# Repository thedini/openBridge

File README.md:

# openBridge

<<<<<<< HEAD
## Abstract

# The set-up

## Initial steps

The Adruino code for this project is based around the NMEA2000 and NMEA2000_Teensyx libraries created by Tino Lappalainen. These are utilized to send the NMEA2000 packets on to the wire.

=======
A project with the purpose of making, exploring and hacking NMEA2000 and marine electronics and making learning achievable without expensive hardware. The ultimate goal is to enable creation of bridge simulations that can be output onto an actual NMEA 2000 bus to enable exploration of the protocol and real world systems at scale. OpenBridge leverages the hard work of the community around these endeavors and hopes to standardize software and hardware as well as adding detailed documentation to low cost exposure to this technology to the wider maritime, engineering and maker/hacker community.

## The Mission

OpenBridge will attempt to leverage exiting work from [CanBoat](https://github.com/canboat/canboat) and [ttlappalaine NMEA 2000](https://github.com/ttlappalainen/NMEA2000) libraries to create a suite of micro-services (containers) that can serve as maritime electronic devices for learning, testing and simulation. By standardizing the hardware and software and having a focus on documentation OpenBridge hopes to make exploration open to groups that would normally not have access or ability to dive into the world of maritime electronics.

Ideally, each micro-service can act as if it is the authentic electronic device using the Teensy as a gateway to an actual ship or test NMEA 2000 bus. OpenBridge will grow to become a curriculum on NMEA 2000 analysis and shipboard security curriculum to provide the basis for self study or teaching! The hope is to give everyone the ability to explore this interesting niche of technology!

## Quick Start

1. Read up on the [CAN Protocol](docs/can_protocol.md)
2. Setup Arduino and Teensy on your system (external links)
3. Load up simple [example code](scr/ARDUINO/working_wind.ino) in Ardino
4. Check out [python documentation](docs/python.md) to extend your capability
5. Fork the repo and build your own!

## The Hardware

The hardware is based on the latest Teensy (4.0 and 4.1). The Teensy provides a huge capability for the price which will lend itself to expansion at a later time. The Teensy also has **three** CAN interfaces to enable further expansion. The Teensy will be mounted on breadboard, perf-board or custom PCB that will enable it to easily connect to an NEMA 2000 bus in a standard fashion. The idea of standardizing on hardware is born from the desire to have a standard platform to develop on and support. As can be expected, most of the associated code and procedures can be adapted for various other platform which are outside the scope of this project. (ESP32, Arduino Mega, Raspberry Pi)

The CAN interfaces will require CAN transceivers (VD230) to accommodate conversion from Can High and Can Low to Can TX and Can RX. These device have been chosen based on their general availability and price.

The system can be built on a Breadboard, or utilize custom PCB to accommodate NMEA 2000 plug. In its simplest implementation it requires little more than a Teensy, the VD230 and some hookup wires.

Specific hardware can be found in the [BoM](docs/bom.md) with board designs in [schmatics](schmatics/)

## Software

The software side of the OpenBridge is going to leverage [ttlappalaine NMEA 2000](https://github.com/ttlappalainen/NMEA2000) and [ttlappalaine's Teeensy Library](https://github.com/ttlappalainen/NMEA2000_Teensyx) as a base. Code is stored in the `src` directory and organized by function. Follow the `docs` to utilize open source code and open hardware to study NMEA2000.

In its most simple implementation you can use OpenBridge to start looking at data with one of many Logic Analyzers and learning how to decipher different parts of the NMEA2000 CAN Frame with the basic **wind sensor**

Extend the capability of the **wind sensor** by feeding your own wind parameters via a csv file.

## UPDATES

19OCT21: Huge push of updated code base. Completely refactored. Plan to add more documentation soon!
>>>>>>> f373c3691c084f3768c9d36196ce28ea740e8996

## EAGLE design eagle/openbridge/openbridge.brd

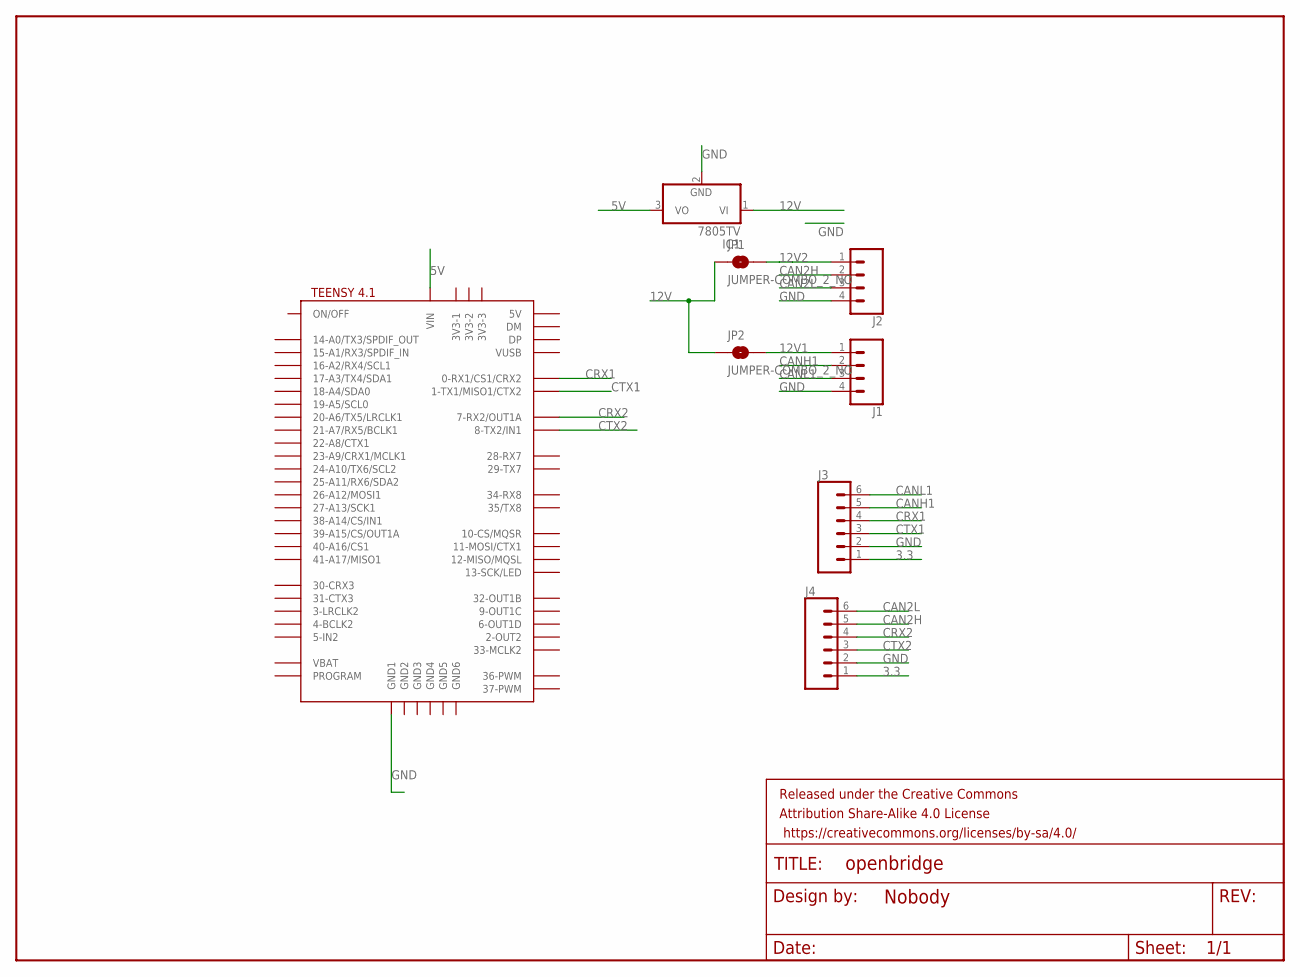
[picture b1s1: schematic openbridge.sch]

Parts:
FRAME1: FRAME-LETTERNO_PACKAGE; DUMMY
IC1: 7805TV; TO220V
J1, J2: CONN_04SCREW; SCREWTERMINAL-3.5MM-4
J3, J4: CONN_06LONGPADS; 1X06_LONGPADS
JP1, JP2: JUMPER-COMBO_2_NO; COMBO-JUMPER_2_NO
U$1: TEENSY41-E; TENNSY41-E

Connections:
3.3: J3.1, J4.1
5V: IC1.3 (VO), U$1.VIN
12V: IC1.1 (VI), JP1.1, JP1.3 (1), JP2.1, JP2.3 (1)
12V1: J1.1, JP2.2, JP2.4 (2)
12V2: J2.1, JP1.2, JP1.4 (2)
CAN2H: J2.2, J4.5
CAN2L: J2.3, J4.6
CANH1: J1.2, J3.5
CANL1: J1.3, J3.6
CRX1: J3.4, U$1.0-RX1/CS1/CRX2
CRX2: J4.4, U$1.7-RX2/OUT1A
CTX1: J3.3, U$1.1-TX1/MISO1/CTX2
CTX2: J4.3, U$1.8-TX2/IN1
GND: IC1.2 (GND), J1.4, J2.4, J3.2, J4.2, U$1.GND1

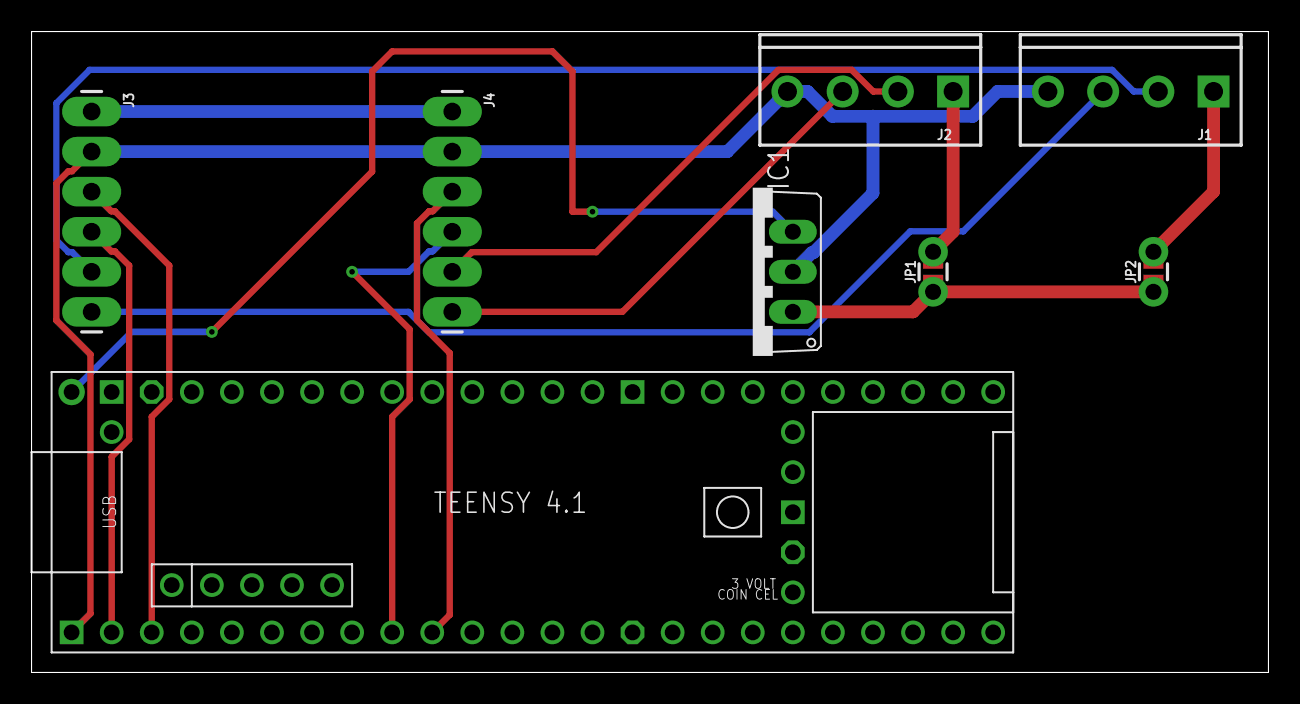
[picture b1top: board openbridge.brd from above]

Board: 2 copper layers, 78.4 x 40.6 mm, 9 parts (0 on the bottom side), 14 nets.

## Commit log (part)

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2021-05-10 Added arduino code that shows proof oc concept
2021-05-10 Addes simple serial interface code in python
2021-05-10 Updated some of the documentation
2021-06-02 adding README
2021-06-02 adding canview doc, specifically Linux install
2021-07-14 Added docker container that runs python file
2021-07-16 adding pgn tool, links and bom
2021-07-22 Update PGN.py
    Removed random string that caused problems at the very end of the program.
2021-07-22 Sent to send data from docker container
2021-07-22 Cleaned up the python
2021-07-25 Remove Docker file
2021-07-25 Allow for dynamic python
2021-07-25 Updated python requirements
2021-07-25 Updated python code
2021-07-25 Sample csv
2021-07-25 Documentation for python scripts
2021-07-25 Added delay between each value sent
2021-07-25 More descriptive prompt
2021-07-25 Set the wind direction to a set value.
2021-07-26 adding BOM and links
2021-07-26 fixing PGN parse issue
2021-07-27 Added multi device arduino code.
2021-07-27 updated to work as both listener and node
2021-07-28 Documentation
2021-07-28 not working yet
2021-07-29 2nd version
2021-07-31 Actually compiles without errors
2021-07-31 Provided sample csv for multi sender
2021-07-31 Renamed sample csv
2021-07-31 Added more comments
2021-08-03 Allows for devicce to look like actual products
2021-08-03 Cleaned up code
2021-08-03 Added search function to find PGN description
2021-08-03 Scrap NMEA2000 website for PGNs and descriptions
2021-08-03 List of PGN's and descriptions
2021-08-03 updated requirements
2021-08-04 adding CAN documentation
2021-08-04 adding NMEA Identifier
2021-08-05 Working wind should actually work now
2021-08-05 Cleaned up data processing on the teensy
2021-08-05 Output string change
2021-08-05 Python script to create fake data based on random vals
2021-08-05 Script to create fake random wind vals
2021-08-06 Updated manual pytho script
2021-08-06 More documentation
2021-08-06 Removed device analyzer
2021-08-06 Fixed links
2021-08-06 adding yacht_devies script
2021-08-06 adding quickstart
2021-10-20 I made a few small changes
2021-10-21 Abstracted out the que to make message sending more uniform
2021-10-21 Added comments
2021-10-25 Changed up the main function to utilize threading
2021-10-31 Removed useless file that was pushed
2022-01-21 adding python docs
2025-08-09 adding logic lab for dc33, will need refresh when not guided

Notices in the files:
parts and their libraries:
SparkFun-Connectors: Licensing: Creative Commons ShareAlike 4.0 International - https://creativecommons.org/licenses/by-sa/4.0
SparkFun-Aesthetics: Released under the Creative Commons Attribution Share-Alike 4.0 License
SparkFun-Aesthetics: https://creativecommons.org/licenses/by-sa/4.0
